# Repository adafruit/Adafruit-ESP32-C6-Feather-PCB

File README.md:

## Adafruit ESP32-C6 Feather - STEMMA QT PCB

<a href="http://www.adafruit.com/products/5933"><br/>
Click here to purchase one from the Adafruit shop</a>

PCB files for the Adafruit ESP32-C6 Feather - STEMMA QT. 

Format is EagleCAD schematic and board layout
* https://www.adafruit.com/product/5933

### Description

The ESP32-C6 is Espressif’s first Wi-Fi 6 SoC integrating 2.4 GHz Wi-Fi 6, Bluetooth 5 (LE) and the 802.15.4 protocol. It brings the goodness you know from the low-cost C3 series and improves it with Zigbee/802.15.4 at 2.4Ghz. That means it could make for great Matter development hardware!

We took our Feather ESP32-S2 and swapped out the 'S2 for a C6. Plus some re-routing and here's what we've got: a C6 Feather with lots of GPIO, lipoly charging and monitoring with the MAX17048, NeoPixel, I2C Stemma QT port, and a second low-quiescent LDO for disabling the I2C and NeoPixel when we want ultra-low power usage - as low as 17uA in deep sleep.

One thing to watch for is that, like the C3, the C6 does not have native USB. It does have a 'built in' USB Serial core that can be used for debugging, but it cannot act like a mouse, keyboard, or disk drive. That means if you are running CircuitPython you will need to use WiFi, Bluetooth or WebSerial for transferring files back and forth rather than drag-and-dropping to a drive. Ditto for the bootloader side, this chip cannot run UF2.

Another thing to be aware of, is  the ESP32-C6 does not have as many GPIO as the ESP32-S2 or ESP32-S3, so A2 is the same GPIO pin as IO6 and A3 is the same pin as IO5. However, this gives it the most compatibility with our existing FeatherWings.

### License

Adafruit invests time and resources providing this open source design, please support Adafruit and open-source hardware by purchasing products from [Adafruit](https://www.adafruit.com)!

Designed by Limor Fried/Ladyada for Adafruit Industries.

Creative Commons Attribution/Share-Alike, all text above must be included in any redistribution. 
See license.txt for additional details.

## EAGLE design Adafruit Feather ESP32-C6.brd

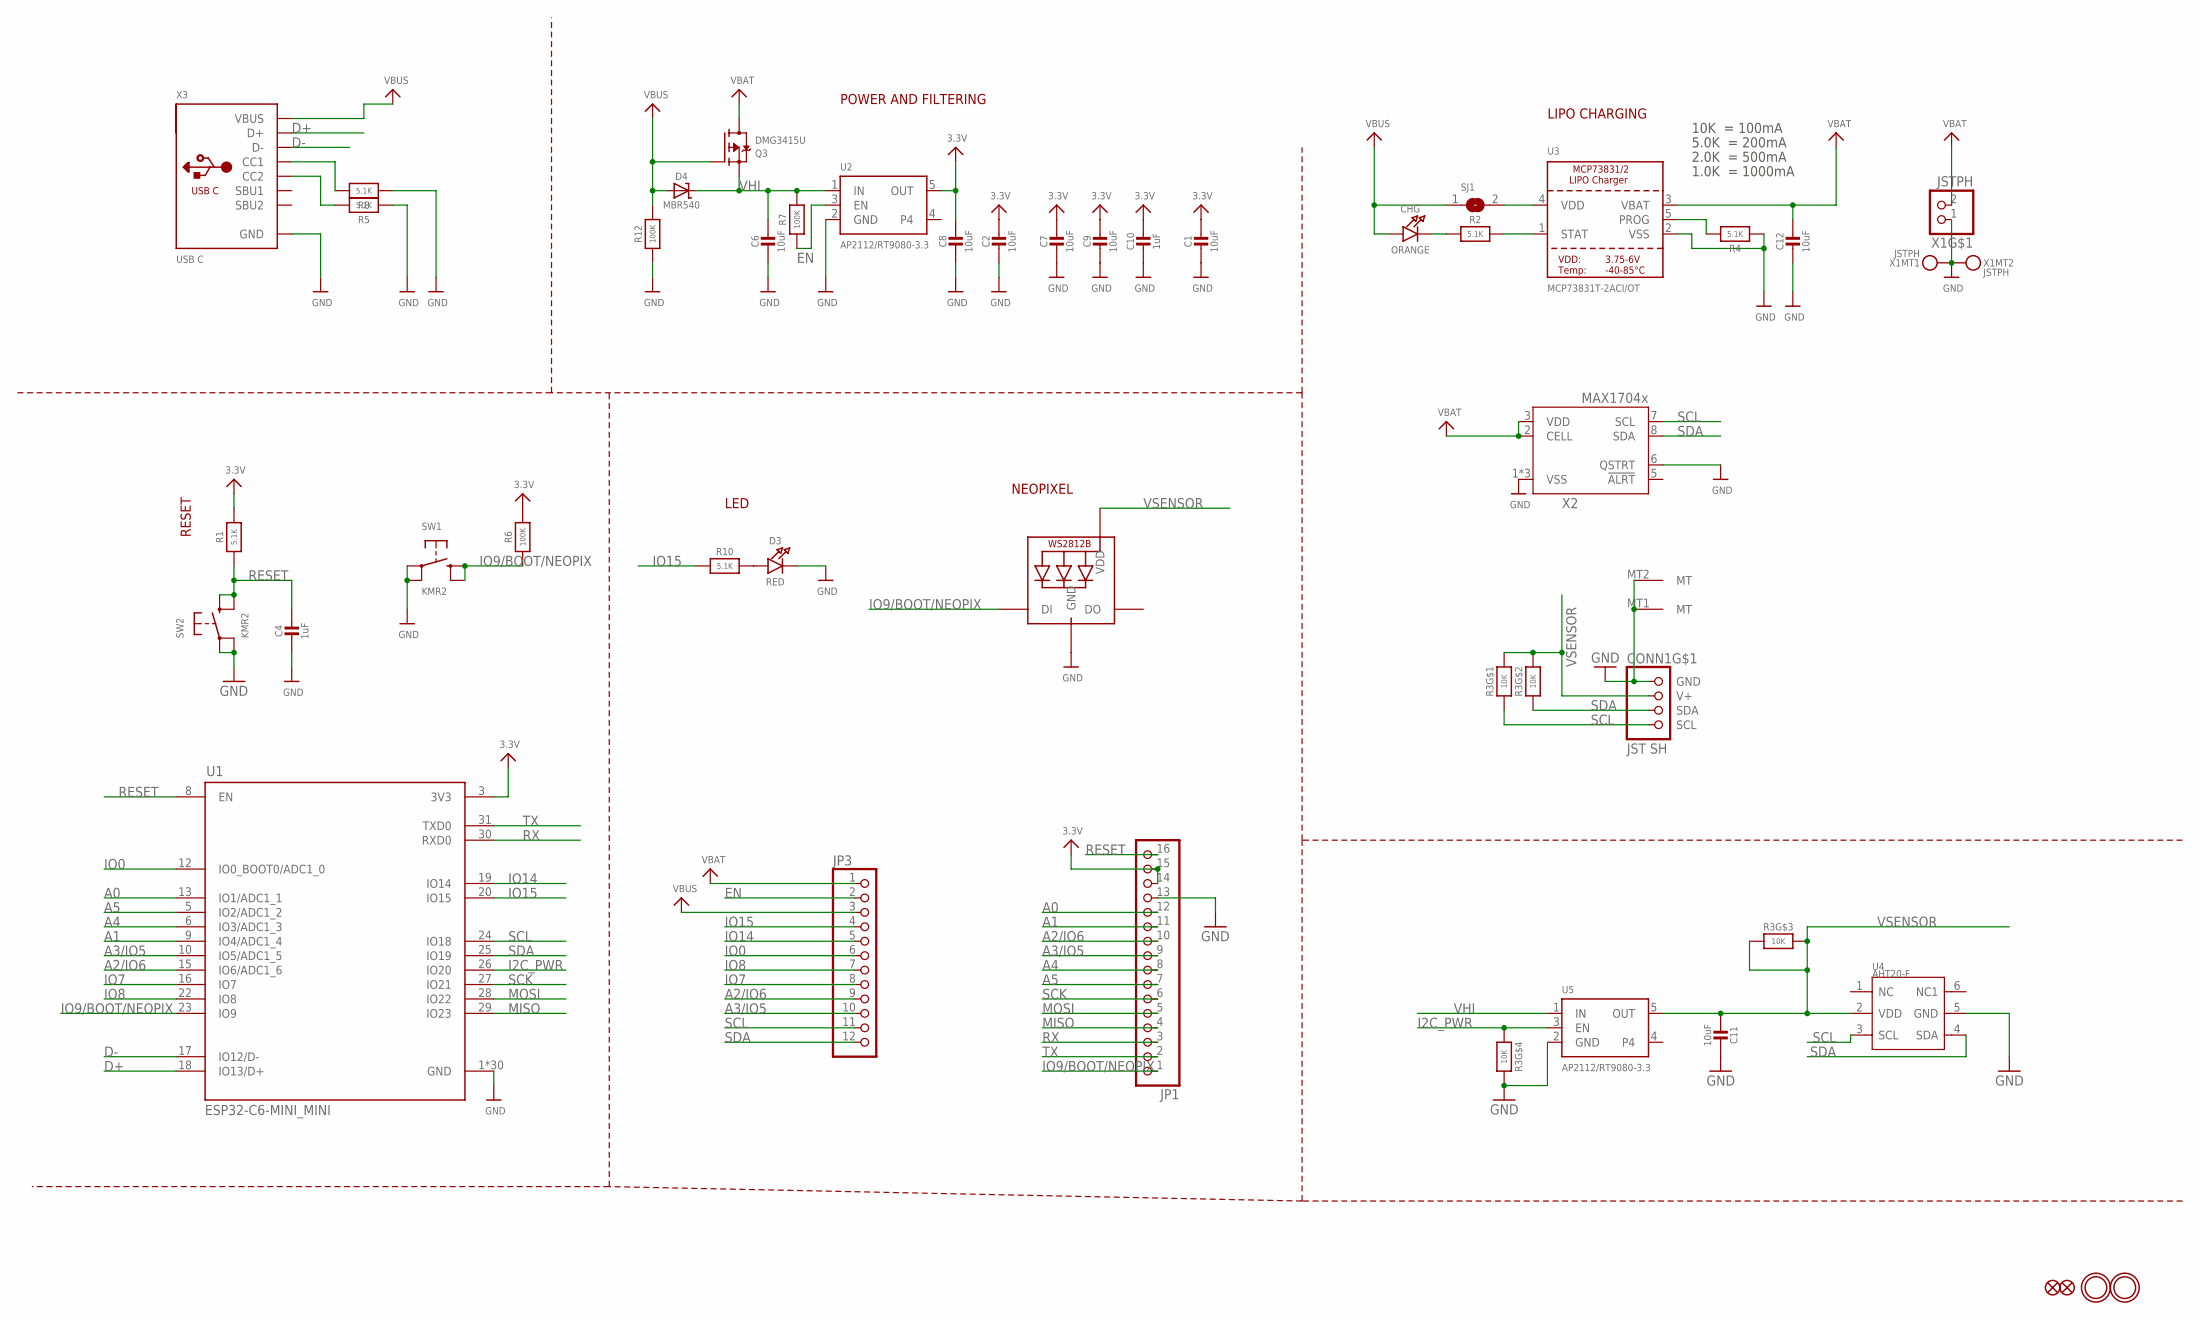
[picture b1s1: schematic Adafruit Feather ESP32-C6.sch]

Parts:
C1, C2, C6, C7, C8, C9, C11: 10uF; 0805-NO
C4, C10: 1uF; 0603-NO
C12: 10uF; _0805MP
CHG: ORANGE; CHIPLED_0603_NOOUTLINE
CONN1: JST SH; JST_SH4_RA
D3: RED; CHIPLED_0603_NOOUTLINE
D4: MBR540; SOD-123
JP1: HEADER-1X16ROUND; 1X16_ROUND
JP3: HEADER-1X12; 1X12_ROUND
LED1: WS2812B_3535FULL; LED3535_FULLPADS
Q3: DMG3415U; SOT23-R
R1, R2, R4, R5, R8, R10: 5.1K; 0603-NO
R3: 10K; RESPACK_4X0603
R6, R7, R12: 100K; 0603-NO
SJ1: SOLDERJUMPERCLOSED; SOLDERJUMPER_CLOSEDWIRE
SW1, SW2: KMR2; BTN_RKB2_4.6X2.8
U1: ESP32-C6-MINI_MINI; ESP32-PICO-MINI
U2, U5: AP2112/RT9080-3.3; SOT23-5; JLC_ROTATION 0
U3: MCP73831T-2ACI/OT; SOT23-5; JLC_ROTATION 0
U4: AHT20-F; LONGAN-IC_SNR6-1.0-3X3X1MM
U$31, U$32: MOUNTINGHOLE2.5; MOUNTINGHOLE_2.5_PLATED
U$34, U$35: FIDUCIAL_1MM
X1: JSTPH; JSTPH2_BATT
X2: MAX17048/T; TDFN8_2X2MM
X3: USB C; USB_C_CUSB31-CFM2AX-01-X

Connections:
3.3V: C1.1, C2.1, C7.1, C8.1, C9.1, C10.1, JP1.14, JP1.15, R1.2, R6.2, U1.3 (3V3), U2.5 (OUT)
A0: JP1.12, U1.13 (IO1/ADC1_1)
A1: JP1.11, U1.9 (IO4/ADC1_4)
A2/IO6: JP1.10, JP3.9, U1.15 (IO6/ADC1_6)
A3/IO5: JP1.9, JP3.10, U1.10 (IO5/ADC1_5)
A4: JP1.8, U1.6 (IO3/ADC1_3)
A5: JP1.7, U1.5 (IO2/ADC1_2)
D+: U1.18 (IO13/D+), X3.A6 (D+), X3.B6 (D+)
D-: U1.17 (IO12/D-), X3.A7 (D-), X3.B7 (D-)
EN: JP3.2, R7.1, U2.3 (EN)
GND: C1.2, C2.2, C4.2, C6.2, C7.2, C8.2, C9.2, C10.2, C11.2, C12.2, CONN1.1 (GND), CONN1.MT1 (MT), CONN1.MT2 (MT), D3.C, JP1.13, LED1.4 (GND), R3.4 (1), R4.1, R5.1, R8.1, R12.1, SW1.A, SW1.A' (P1), SW2.A, SW2.A' (P1), U1.1 (GND), U1.2 (GND), U1.11 (GND), U1.14 (GND), U1.36 (GND), U1.37 (GND), U1.38 (GND), U1.39 (GND), U1.40 (GND), U1.41 (GND), U1.42 (GND), U1.43 (GND), U1.44 (GND), U1.45 (GND), U1.46 (GND), U1.47 (GND), U1.48 (GND), U1.49 (GND), U1.50 (GND), U1.51 (GND), U1.52 (GND), U1.53 (GND), U1.54 (GND), U1.55 (GND), U1.56 (GND), U1.57 (GND), U1.58 (GND), U1.59 (GND), U1.60 (GND), U1.61 (GND), U2.2 (GND), U3.2 (VSS), U4.5 (GND), U5.2 (GND), X1.1, X1.NC1, X1.NC2, X2.1 (VSS), X2.4 (VSS), X2.6 (QSTRT), X2.THERMAL (VSS), X3.A1B12 (GND), X3.B1A12 (GND)
I2C_PWR: R3.5 (2), U1.26 (IO20), U5.3 (EN)
IO0: JP3.6, U1.12 (IO0_BOOT0/ADC1_0)
IO7: JP3.8, U1.16 (IO7)
IO8: JP3.7, U1.22 (IO8)
IO9/BOOT/NEOPIX: JP1.1, LED1.1 (DI), R6.1, SW1.B (S), SW1.B' (S1), U1.23 (IO9)
IO14: JP3.5, U1.19 (IO14)
IO15: JP3.4, R10.1, U1.20 (IO15)
MISO: JP1.4, U1.29 (IO23)
MOSI: JP1.5, U1.28 (IO22)
unnamed: CHG.C, R2.1
unnamed: SJ1.2, U3.4 (VDD)
unnamed: R2.2, U3.1 (STAT)
unnamed: R4.2, U3.5 (PROG)
unnamed: D3.A, R10.2
unnamed: R8.2, X3.A5 (CC1)
unnamed: R5.2, X3.B5 (CC2)
RESET: C4.1, JP1.16, R1.1, SW2.B (S), SW2.B' (S1), U1.8 (EN)
RX: JP1.3, U1.30 (RXD0)
SCK: JP1.6, U1.27 (IO21)
SCL: CONN1.4 (SCL), JP3.11, R3.1, U1.24 (IO18), U4.3 (SCL), X2.7 (SCL)
SDA: CONN1.3 (SDA), JP3.12, R3.2 (1), U1.25 (IO19), U4.4 (SDA), X2.8 (SDA)
TX: JP1.2, U1.31 (TXD0)
VBAT: C12.1, JP3.1, Q3.3 (D), U3.3 (VBAT), X1.2, X2.2 (CELL), X2.3 (VDD)
VBUS: CHG.A, D4.A, JP3.3, Q3.1 (G), R12.2, SJ1.1, X3.A4B9 (VBUS), X3.B4A9 (VBUS)
VHI: C6.1, D4.C, Q3.2 (S), R7.2, U2.1 (IN), U5.1 (IN)
VSENSOR: C11.1, CONN1.2 (V+), LED1.2 (VDD), R3.3 (1), R3.6 (2), R3.7 (2), R3.8 (2), U4.2 (VDD), U5.5 (OUT)

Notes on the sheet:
POWER AND FILTERING
RESET
10K = 100mA
5.0K = 200mA
2.0K = 500mA
1.0K = 1000mA
LIPO CHARGING
LED
NEOPIXEL

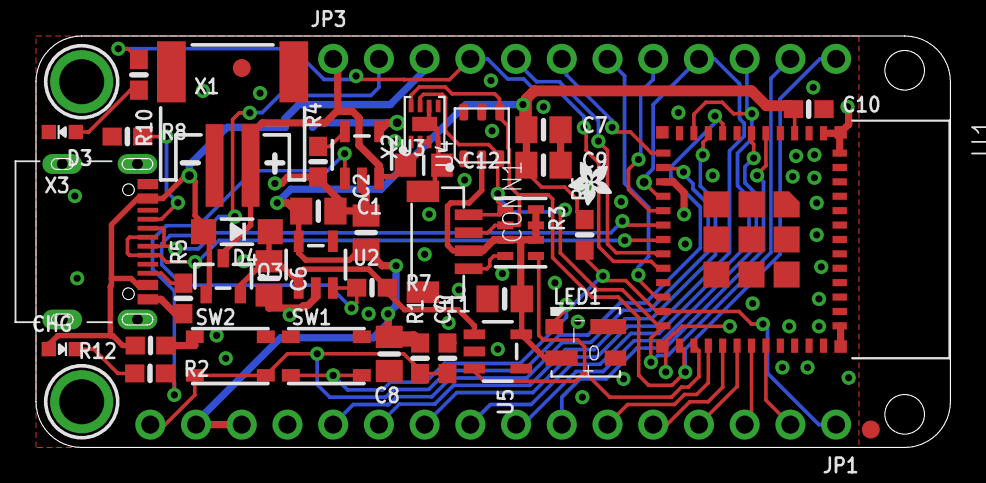
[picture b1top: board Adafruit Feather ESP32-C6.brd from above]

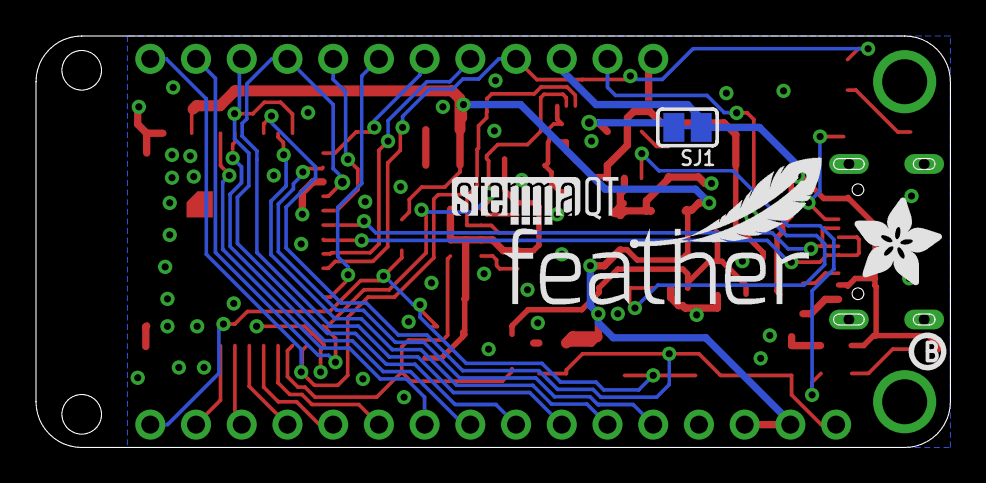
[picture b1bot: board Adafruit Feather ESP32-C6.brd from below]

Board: 2 copper layers, 50.8 x 22.9 mm, 115 parts (36 on the bottom side), 37 nets.

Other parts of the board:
PLABEL0: PLABEL0
PLABEL1: PLABEL1
PLABEL2: PLABEL2
PLABEL4: PLABEL4
PLABEL5: PLABEL5
PLABEL6: PLABEL6
PLABEL7: PLABEL7
PLABEL8: PLABEL8
PLABEL9: PLABEL9
PLABEL10: PLABEL10
PLABEL11: PLABEL11
PLABEL12: PLABEL12
PLABEL13: PLABEL13
PLABEL14: PLABEL14
PLABEL15: PLABEL15
PLABEL16: PLABEL16
PLABEL17: PLABEL17
PLABEL18: PLABEL18
PLABEL19: PLABEL19
PLABEL20: PLABEL20
PLABEL21: PLABEL21
PLABEL22: PLABEL22
PLABEL23: PLABEL23
PLABEL24: PLABEL24
PLABEL25: PLABEL25
PLABEL26: PLABEL26
PLABEL27: PLABEL27
PLABEL28: PLABEL28
PLABEL29: PLABEL29
PLABEL30: PLABEL30
PLABEL31: PLABEL31
PLABEL32: PLABEL32
PLABEL33: PLABEL33
PLABEL34: PLABEL34
PLABEL35: PLABEL35
PLABEL36: PLABEL36
PLABEL37: PLABEL37
PLABEL38: PLABEL38
PLABEL39: PLABEL39
PLABEL40: PLABEL40
PLABEL41: PLABEL41
PLABEL42: PLABEL42
PLABEL43: PLABEL43
PLABEL44: PLABEL44
PLABEL45: PLABEL45
PLABEL46: PLABEL46
PLABEL47: PLABEL47
PLABEL48: PLABEL48
PLABEL49: PLABEL49
PLABEL51: PLABEL51
PLABEL52: PLABEL52
PLABEL53: PLABEL53
PLABEL54: PLABEL54
PLABEL55: PLABEL55
PLABEL56: PLABEL56
PLABEL57: PLABEL57
PLABEL58: PLABEL58
PLABEL59: PLABEL59
PLABEL60: PLABEL60
PLABEL61: PLABEL61
PLABEL62: PLABEL62
PLABEL63: PLABEL63
PLABEL64: PLABEL64
PLABEL65: PLABEL65
PLABEL66: PLABEL66
PLABEL67: PLABEL67
PLABEL68: PLABEL68
U$14: PCBFEAT-REV-040
U$15: FEATHERLOGO_MED
U$26: ADAFRUIT_2.5MM
U$48: ADAFRUIT_5MM
U$53: STEMMAQT

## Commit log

2024-08-15 cookiecutter
2024-08-20 prettypins
2024-08-20 factory reset bin
    tested with https://espressif.github.io/esptool-js/
2024-08-22 power pin name
2025-09-24 Corrected battery connector

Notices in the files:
parts and their libraries:
microbuilder: This work is placed in the public domain, and may be freely used for commercial and non-commercial work with the following conditions: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
